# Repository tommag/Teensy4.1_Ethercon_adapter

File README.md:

# Teensy 4.1 etherCON adapter

These are the design files to add a Neutrik etherCON Ethernet connector to your Teensy 4.1. It replaces the official [Ethernet kit for Teensy 4.1](https://www.pjrc.com/store/ethernet_kit.html) sold by PJRC and provides a panel-mountable, rugged Ethernet port to your Teensy.

## Get the PCB made

Order from OSHPark here : https://oshpark.com/shared_projects/l8queh8X

Or you can get the PCB made by the board house of your choice, just send them the .zip file in the `gerber` directory.

## Bill of materials

| Designator  | Qty | Value      | Package                                          | Farnell P/N | Mouser P/N        | Digikey P/N       |
|---|---|---|---|---|---|---|
| C1          |  1  | 0.1uF/50V  | C_0805_2012Metric                                | 3013478     | 581-08055C104K    | 1276-1003-1-ND    |
| C2          |  1  | 1000pF/2kV | C_0805_2012Metric                                |	2522440	    |	791-0805B102K102CT|	311-4341-1-ND     |
| D1          |  1  | LED        | LED_1206_3216Metric						                  |             |                   |                   |
| J1          |  2  | Conn_01x06 | PinHeader_2x03_P2mm_Vertical						          |             |                   |                   |
| J2          |  1  | NE8FAV     | Neutrik_EtherCON_NE8FAV_1x8P_GND_Female_Vertical	| 1202031	    |	568-NE8FAV        |                   |
| R4,R3,R2,R1 |  4  | 75R        | R_0805_2012Metric                                | 2671086	    |	652-CR0805JW-750ELF| RR12Q75DCT-ND    |
| TR1         |  1  | PT61017PEL | Transformer_Ethernet_Bourns_PT61017PEL           |             | 652-PT61017PEL    |	PT61017PELCT-ND   |

You will also need **1mm pitch** 6 conductors ribbon cable and 2 **2mm pitch** female IDC connectors to connect the Teensy and the etherCON adapter. 

## Assembly steps
Check out the html interactive BoM in the `bom` directory.

1. Solder the passive components. You don't need a stencil and solder paste, a soldering iron with fine tip is OK.

2. Solder the LAN magnetics. 

3. Solder the 2mm pin header and the etherCON jack

4. Solder a 2mm pin header to your Teensy 4.1

5. Connect the etherCON adapter to the Teensy with a ribbon cable (pay attention to the connector orientation)

Just like the Ethernet kit, you need to use the `NativeEthernet` library to use the integrated Ethernet port.

On the bottom right of the PCB, you can see an unused 0805 footprint (R5 in the design files). If you need (and you know better than me), you can cut the trace under the footprint and handle differently the Ethernet grounding.

6. Enjoy a panel mount, professionnal-looking Ethernet port for your Teensy!

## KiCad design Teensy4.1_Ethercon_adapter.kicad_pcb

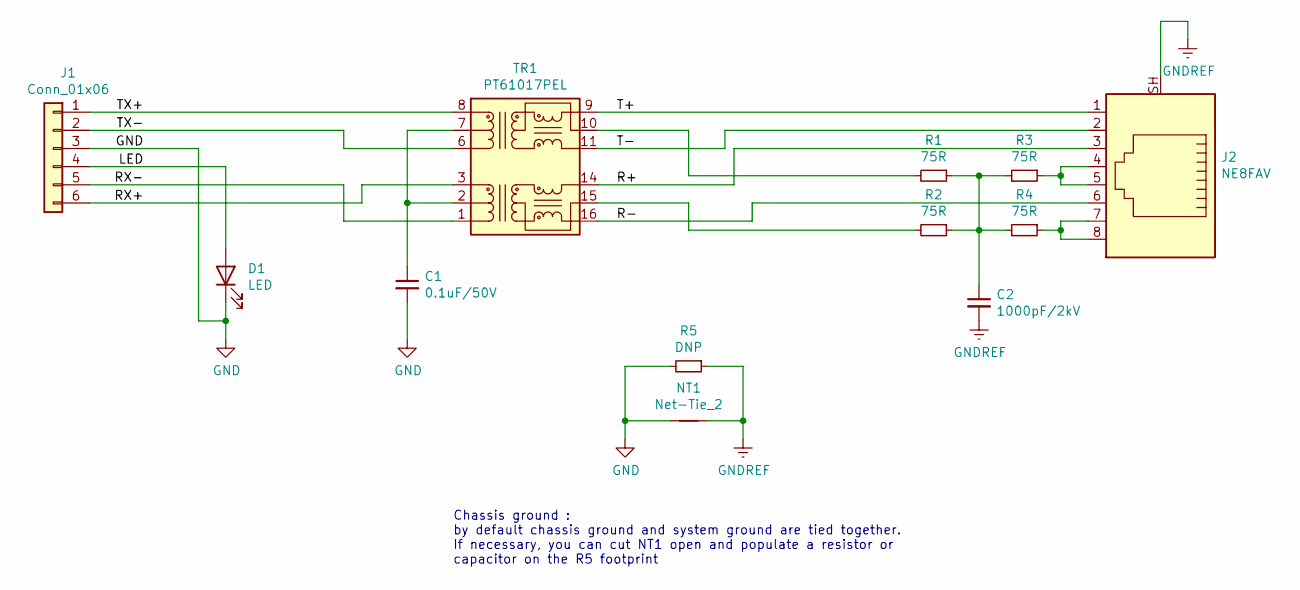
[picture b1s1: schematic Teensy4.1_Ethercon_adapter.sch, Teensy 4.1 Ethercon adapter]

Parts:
C1: 0.1uF/50V; C_0805_2012Metric
C2: 1000pF/2kV; C_0805_2012Metric
D1: LED; LED_1206_3216Metric
J1: Conn_01x06; PinHeader_2x03_P2.00mm_Vertical
J2: NE8FAV; Neutrik_EtherCON_NE8FAV_1x8P_GND_Female_Vertical
NT1: Net-Tie_2; NetTie-2_SMD_Pad0.5mm
R1, R2, R3, R4: 75R; R_0805_2012Metric
R5: DNP; R_0805_2012Metric
TR1: PT61017PEL; Transformer_Ethernet_Bourns_PT61017PEL

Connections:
/LED: D1.2 (A), J1.4
/R+: J2.3, TR1.14 (TX-)
/R-: J2.6, TR1.16 (TX+)
/RX+: J1.6, TR1.3 (TD-)
/RX-: J1.5, TR1.1 (TD+)
/T+: J2.1, TR1.9 (RX-)
/T-: J2.2, TR1.11 (RX+)
/TX+: J1.1, TR1.8 (RD-)
/TX-: J1.2, TR1.6 (RD+)
GND: C1.2, D1.1 (K), J1.3, NT1.1, R5.2
GNDREF: C2.2, J2.SH, NT1.2, R5.1
unnamed: C1.1, TR1.2 (C_TD), TR1.7 (C_RD)
unnamed: C2.1, R1.1, R2.1, R3.2, R4.2
unnamed: J2.4, J2.5, R3.1
unnamed: J2.7, J2.8, R4.1
unnamed: R1.2, TR1.10 (C_RX)
unnamed: R2.2, TR1.15 (C_TX)

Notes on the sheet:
Chassis ground : by default chassis ground and system ground are tied together. If necessary, you can cut NT1 open and populate a resistor or capacitor on the R5 footprint

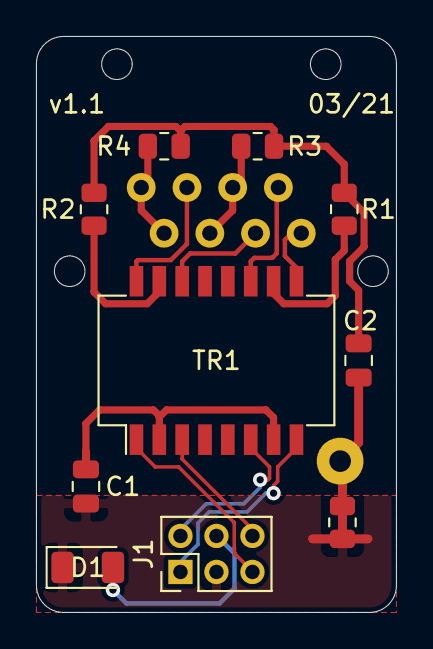
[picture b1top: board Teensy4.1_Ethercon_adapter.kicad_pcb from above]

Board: 2 copper layers, 20.0 x 32.0 mm, 12 parts (1 on the bottom side), 17 nets.

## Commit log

2021-01-28 First commit v1.0
2021-03-31 Version 1.1 - fixed routing and pin header pitch (2mm)
2021-03-31 Add pictures
2021-03-31 Add picture
